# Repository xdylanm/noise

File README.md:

# Random Noise

A module in the Eurorack format for generating various types of noise.

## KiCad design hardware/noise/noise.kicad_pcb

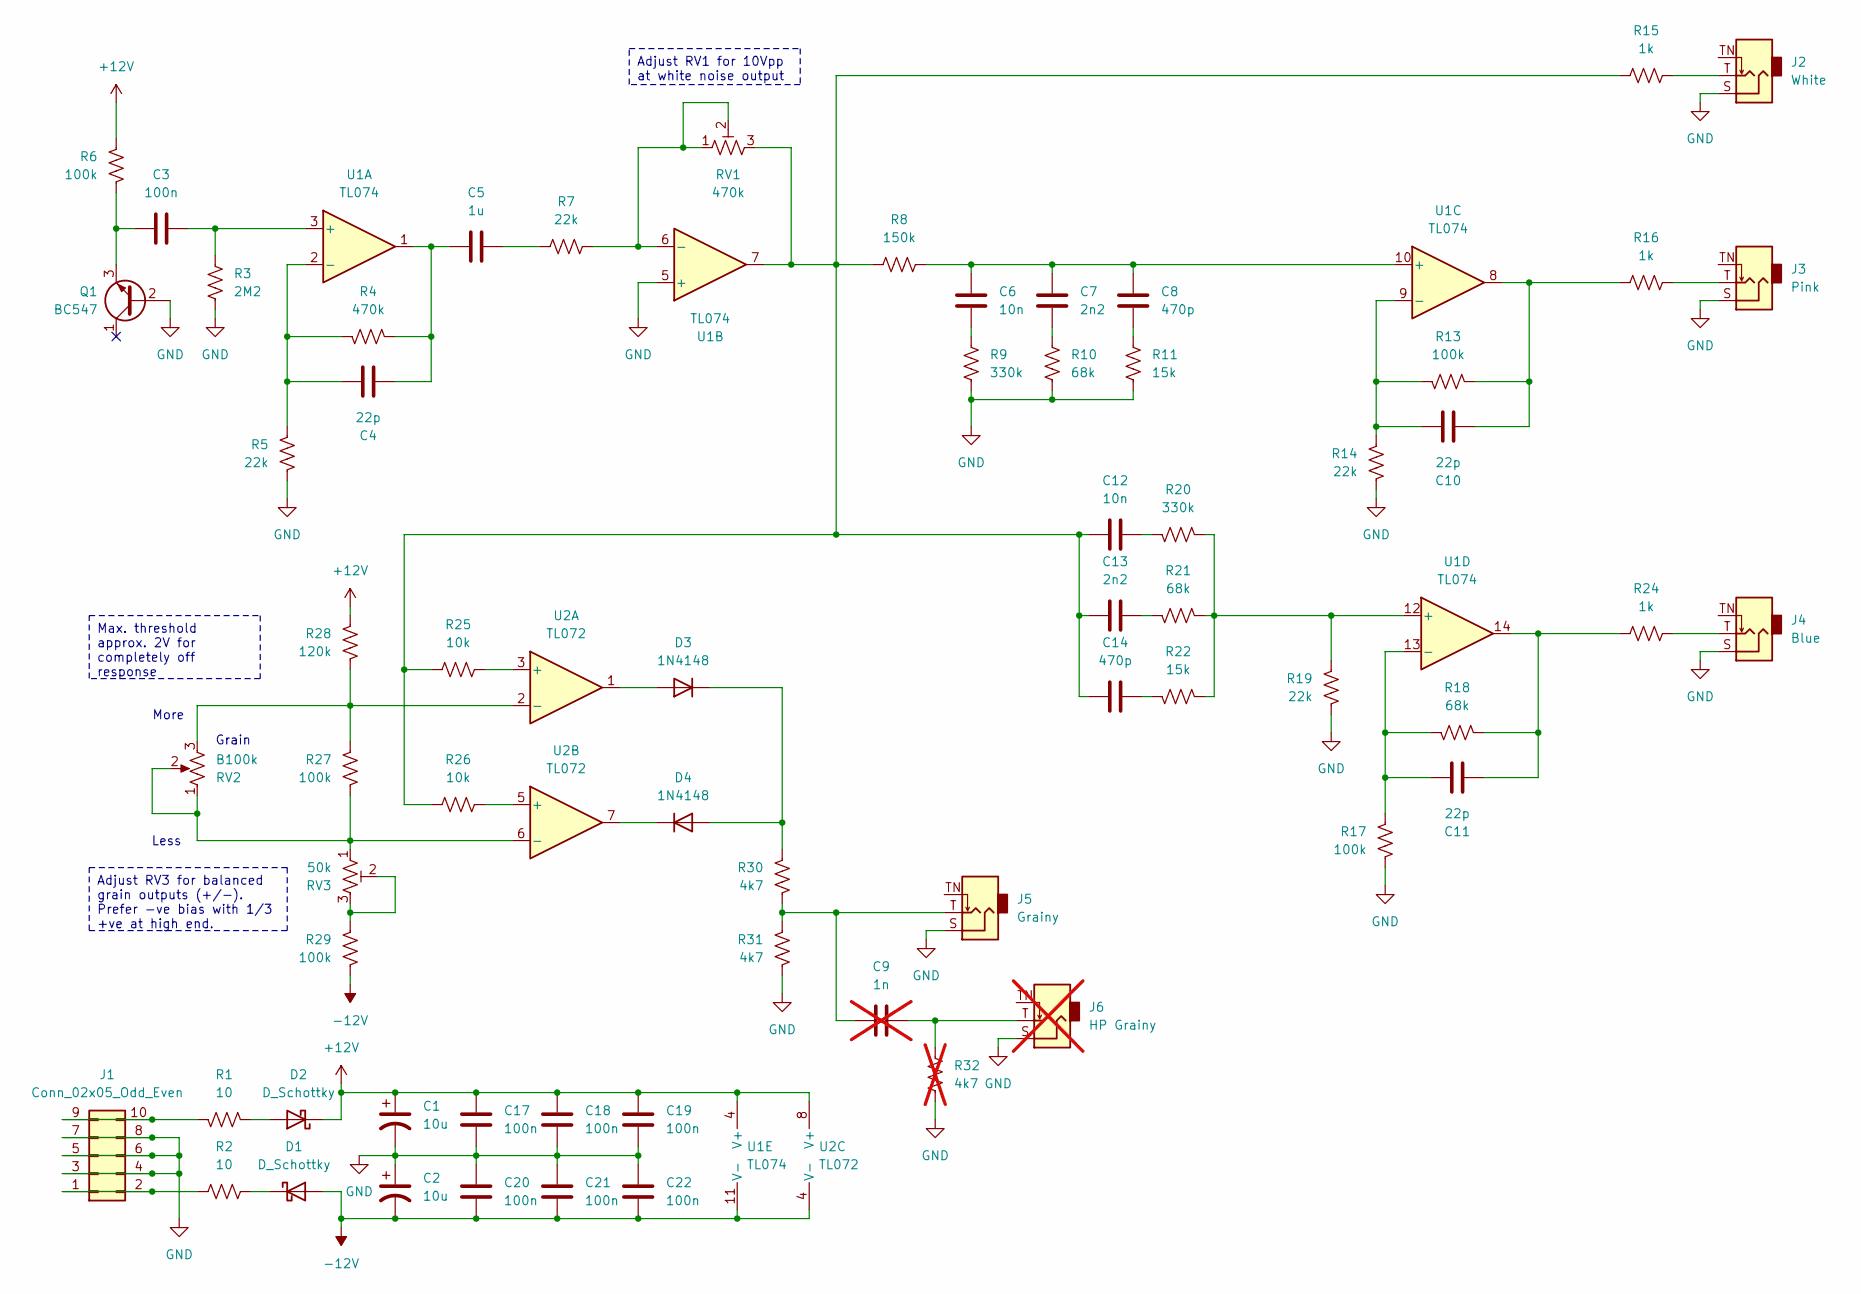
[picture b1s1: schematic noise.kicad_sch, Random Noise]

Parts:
C1, C2: 10u; CP_Radial_D5.0mm_P2.50mm
C3, C17, C18, C19, C20, C21, C22: 100n; C_Disc_D5.0mm_W2.5mm_P5.00mm
C4, C10, C11: 22p; C_Disc_D5.0mm_W2.5mm_P5.00mm
C5: 1u; C_Disc_D5.0mm_W2.5mm_P5.00mm
C6, C12: 10n; C_Rect_L7.0mm_W3.5mm_P5.00mm
C7, C13: 2n2; C_Rect_L7.0mm_W3.5mm_P5.00mm
C8, C14: 470p; C_Disc_D4.7mm_W2.5mm_P5.00mm
C9: 1n; C_Rect_L7.0mm_W3.5mm_P5.00mm; not fitted
D1, D2: D_Schottky; D_DO-41_SOD81_P3.81mm_Vertical_AnodeUp
D3, D4: 1N4148; D_DO-35_SOD27_P7.62mm_Horizontal
J1: Conn_02x05_Odd_Even; IDC-Header_2x05_P2.54mm_Horizontal
J2: White; Jack_3.5mm_QingPu_WQP-PJ323M_Horizontal
J3: Pink; Jack_3.5mm_QingPu_WQP-PJ323M_Horizontal
J4: Blue; Jack_3.5mm_QingPu_WQP-PJ323M_Horizontal
J5: Grainy; Jack_3.5mm_QingPu_WQP-PJ323M_Horizontal
J6: HP Grainy; Jack_3.5mm_QingPu_WQP-PJ323M_Horizontal; not fitted
Q1: BC547; TO-92_Inline_Wide
R1: 10; R_Axial_DIN0207_L6.3mm_D2.5mm_P10.16mm_Horizontal
R2: 10; R_Axial_DIN0207_L6.3mm_D2.5mm_P2.54mm_Vertical
R3: 2M2; R_Axial_DIN0204_L3.6mm_D1.6mm_P2.54mm_Vertical
R4: 470k; R_Axial_DIN0204_L3.6mm_D1.6mm_P2.54mm_Vertical
R5, R7, R14, R19: 22k; R_Axial_DIN0204_L3.6mm_D1.6mm_P2.54mm_Vertical
R6, R13, R17, R29: 100k; R_Axial_DIN0204_L3.6mm_D1.6mm_P2.54mm_Vertical
R8: 150k; R_Axial_DIN0204_L3.6mm_D1.6mm_P2.54mm_Vertical
R9, R20: 330k; R_Axial_DIN0204_L3.6mm_D1.6mm_P2.54mm_Vertical
R10, R18, R21: 68k; R_Axial_DIN0204_L3.6mm_D1.6mm_P2.54mm_Vertical
R11, R22: 15k; R_Axial_DIN0204_L3.6mm_D1.6mm_P2.54mm_Vertical
R15, R24: 1k; R_Axial_DIN0204_L3.6mm_D1.6mm_P2.54mm_Vertical
R16: 1k; R_Axial_DIN0207_L6.3mm_D2.5mm_P10.16mm_Horizontal
R25, R26: 10k; R_Axial_DIN0204_L3.6mm_D1.6mm_P2.54mm_Vertical
R27: 100k; R_Axial_DIN0207_L6.3mm_D2.5mm_P10.16mm_Horizontal
R28: 120k; R_Axial_DIN0204_L3.6mm_D1.6mm_P7.62mm_Horizontal
R30: 4k7; R_Axial_DIN0204_L3.6mm_D1.6mm_P7.62mm_Horizontal
R31: 4k7; R_Axial_DIN0204_L3.6mm_D1.6mm_P2.54mm_Vertical
R32: 4k7; R_Axial_DIN0204_L3.6mm_D1.6mm_P2.54mm_Vertical; not fitted
RV1: 470k; Potentiometer_Piher_PT-6-V_Vertical
RV2: B100k; Potentiometer_Bourns_PTV09A-2_Single_Horizontal
RV3: 50k; Potentiometer_Piher_PT-6-V_Vertical
U1: TL074; DIP-14_W7.62mm_Socket
U2: TL072; DIP-8_W7.62mm_Socket

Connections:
+12V: C1.1, C17.2, C18.2, C19.2, D2.1 (K), R6.1, R28.1, U1.4 (V+), U2.8 (V+)
-12V: C2.2, C20.1, C21.1, C22.1, D1.2 (A), R29.2, U1.11 (V-), U2.4 (V-)
GND: C1.2, C2.1, C17.1, C18.1, C19.1, C20.2, C21.2, C22.2, J1.3, J1.4, J1.5, J1.6, J1.7, J1.8, J2.S, J3.S, J4.S, J5.S, J6.S, Q1.2 (B), R3.2, R5.2, R9.2, R10.2, R11.2, R14.2, R17.2, R19.2, R31.2, R32.2, U1.5 (+)
unnamed: C4.2, C5.1, R4.2, U1.1
unnamed: C5.2, R7.1
unnamed: C6.1, R9.1
unnamed: C7.1, R10.1
unnamed: C8.1, R11.1
unnamed: C9.1, J6.T, R32.1
unnamed: C9.2, J5.T, R30.2, R31.1
unnamed: C10.2, R13.2, R16.1, U1.8
unnamed: C11.2, R18.2, R24.1, U1.14
unnamed: C12.1, R20.1
unnamed: C12.2, C13.2, C14.2, R8.1, R15.1, R25.1, R26.1, RV1.3, U1.7
unnamed: C13.1, R21.1
unnamed: C14.1, R22.1
unnamed: D1.1 (K), R2.2
unnamed: D2.2 (A), R1.2
unnamed: D3.2 (A), U2.1
unnamed: D3.1 (K), D4.2 (A), R30.1
unnamed: D4.1 (K), U2.7
unnamed: J1.1, J1.2, R2.1
unnamed: J1.9, J1.10, R1.1
unnamed: J2.T, R15.2
unnamed: J3.T, R16.2
unnamed: J4.T, R24.2
unnamed: C3.1, Q1.3 (E), R6.2
unnamed: R29.1, RV3.2, RV3.3
unnamed: C3.2, R3.1, U1.3 (+)
unnamed: C4.1, R4.1, R5.1, U1.2 (-)
unnamed: R7.2, RV1.1, RV1.2, U1.6 (-)
unnamed: C6.2, C7.2, C8.2, R8.2, U1.10 (+)
unnamed: C10.1, R13.1, R14.1, U1.9 (-)
unnamed: R19.1, R20.2, R21.2, R22.2, U1.12 (+)
unnamed: C11.1, R17.1, R18.1, U1.13 (-)
unnamed: R25.2, U2.3 (+)
unnamed: R27.1, R28.2, RV2.3, U2.2 (-)
unnamed: R26.2, U2.5 (+)
unnamed: R27.2, RV2.1, RV2.2, RV3.1, U2.6 (-)

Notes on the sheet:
Adjust RV1 for 10Vpp at white noise output
Max. threshold approx. 2V for completely off response
Adjust RV3 for balanced grain outputs (+/-). Prefer -ve bias with 1/3 +ve at high end.
Grain
More
Less

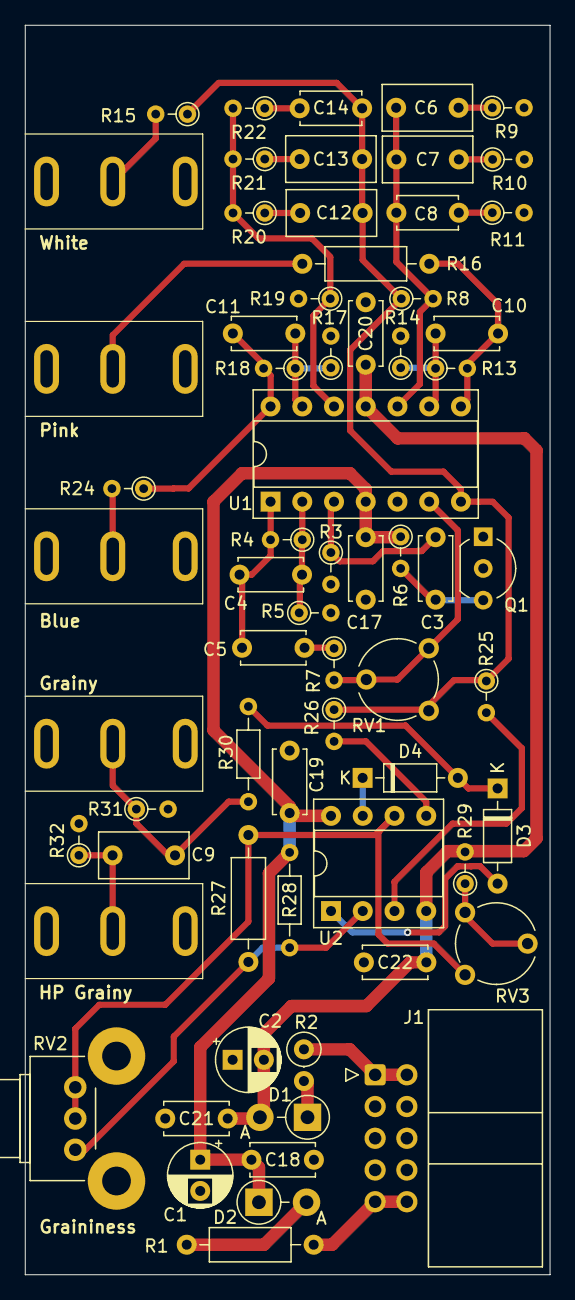
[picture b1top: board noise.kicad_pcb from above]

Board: 2 copper layers, 42.0 x 100.0 mm, 66 parts (0 on the bottom side), 39 nets.

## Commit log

2025-03-08 Initial design and analysis with fractional filter for pink noise. Includes validating measurments for first and second stage gains for white noise and FLPF pink noise spectrum
2025-03-09 finished design checks on grain output and update schematic/layout to v1.1
2025-03-09 Submitted board v1.1 for fab
2025-03-12 Fixed bad orientation for IDC header to support horizontal and vertical plugs
2025-12-16 PCB silk tidy-up and added faceplate
2025-12-16 Converted docs to mkdocs
2025-12-16 Updating gitignore, adding csvs for BOM and data
2025-12-29 Doc cleanup, assembly guide, faceplate art

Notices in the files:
hardware/noise/noise.kicad_pcb:
CC BY-SA 4.0
idyllm CC BY-SA 4.0
